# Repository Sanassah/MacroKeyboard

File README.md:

# Macrokeyboard with Raspberry Pi Pico

## Overview
This project is my first experience in CAD for 3D modeling and printing and also my first experience in PCB design and manufacturing. It involves creating a macrokeyboard with **9 keys** and **2 knobs** using a **Raspberry Pi Pico** microcontroller. The custom PCB was designed using **KiCad**.

## Features
- **Microcontroller:** Raspberry Pi Pico
- **Inputs:** 
  - 9 Keys
  - 2 Knobs (Rotary Encoders)
- **Software:** Python on Raspberry Pi Pico

## PCB Design
The PCB was custom-designed using KiCad.

## Final Result
Here is the final assembled macrokeyboard:

<div align="center">

</div>

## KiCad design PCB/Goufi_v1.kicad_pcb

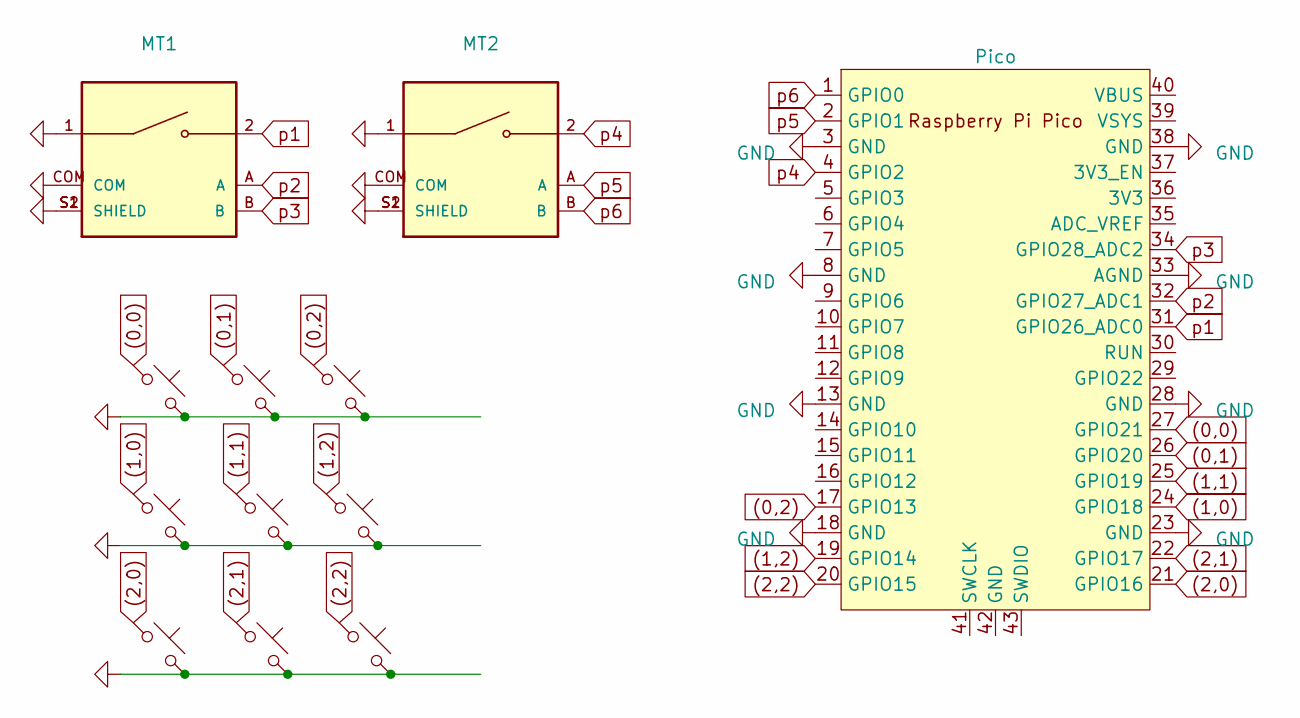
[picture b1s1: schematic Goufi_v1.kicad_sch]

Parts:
MT1, MT2: PEC11R-4215F-S0024; XDCR_PEC11R-4215F-S0024; PARTREV Rev. 09/19
MX1, MX2, MX3, MX4, MX5, MX6, MX7, MX8, MX9: MX_SW_solder; SW_MX_1u
U1: Pico; RPi_Pico_SMD_TH

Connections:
(0,0): MX1.1, U1.27 (GPIO21)
(0,1): MX4.1, U1.26 (GPIO20)
(0,2): MX7.1, U1.17 (GPIO13)
(1,0): MX2.1, U1.24 (GPIO18)
(1,1): MX5.1, U1.25 (GPIO19)
(1,2): MX8.1, U1.19 (GPIO14)
(2,0): MX3.1, U1.21 (GPIO16)
(2,1): MX6.1, U1.22 (GPIO17)
(2,2): MX9.1, U1.20 (GPIO15)
GND: MT1.1, MT1.COM, MT1.S1 (SHIELD), MT1.S2 (SHIELD), MT2.1, MT2.COM, MT2.S1 (SHIELD), MT2.S2 (SHIELD), MX1.2, MX2.2, MX3.2, MX4.2, MX5.2, MX6.2, MX7.2, MX8.2, MX9.2, U1.3 (GND), U1.8 (GND), U1.13 (GND), U1.18 (GND), U1.23 (GND), U1.28 (GND), U1.33 (AGND), U1.38 (GND)
p1: MT1.2, U1.31 (GPIO26_ADC0)
p2: MT1.A, U1.32 (GPIO27_ADC1)
p3: MT1.B, U1.34 (GPIO28_ADC2)
p4: MT2.2, U1.4 (GPIO2)
p5: MT2.A, U1.2 (GPIO1)
p6: MT2.B, U1.1 (GPIO0)

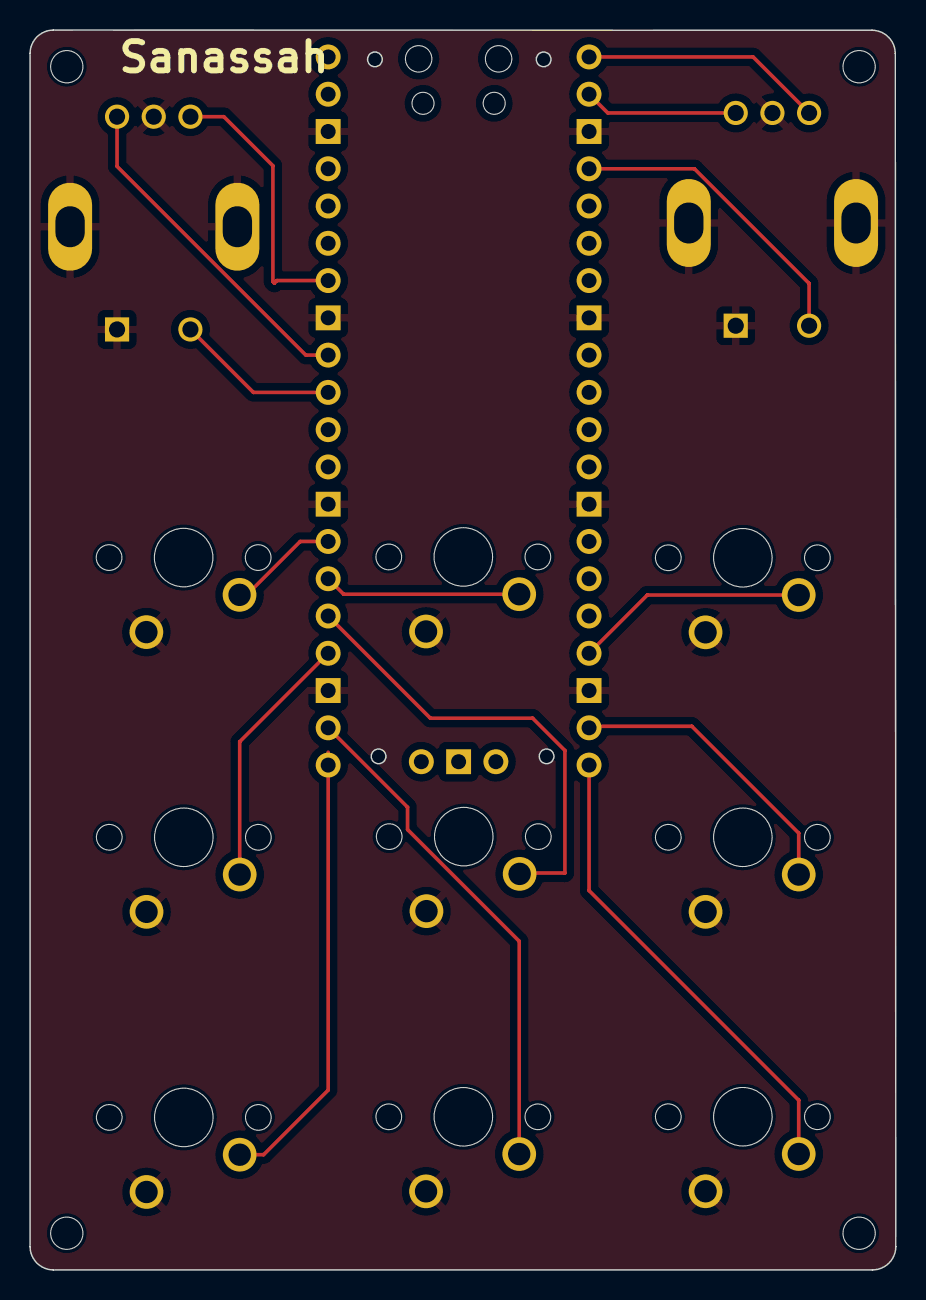
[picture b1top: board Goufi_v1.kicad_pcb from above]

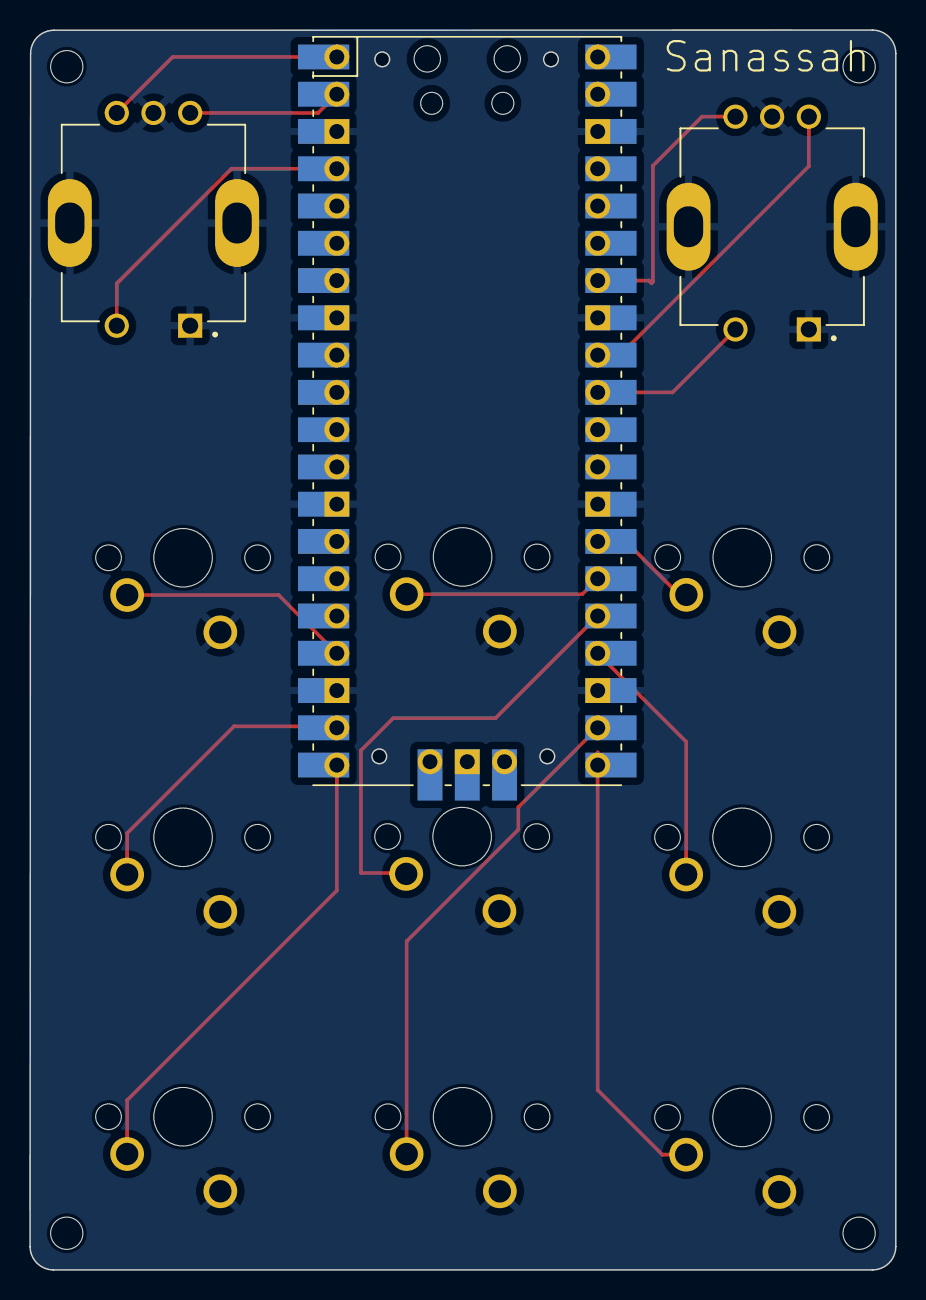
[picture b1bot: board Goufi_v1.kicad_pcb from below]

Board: 2 copper layers, 59.0 x 84.5 mm, 12 parts (3 on the bottom side), 16 nets.
